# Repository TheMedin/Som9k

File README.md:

# Som9k
Principles of Digital Fabrication, group project

Soil o moisturizer 9000 is a gadget for automatically watering plants. It consists of a waterbottle, a moisture sensor, a valve controlled by a microcontroller, and a tube to guide the water.

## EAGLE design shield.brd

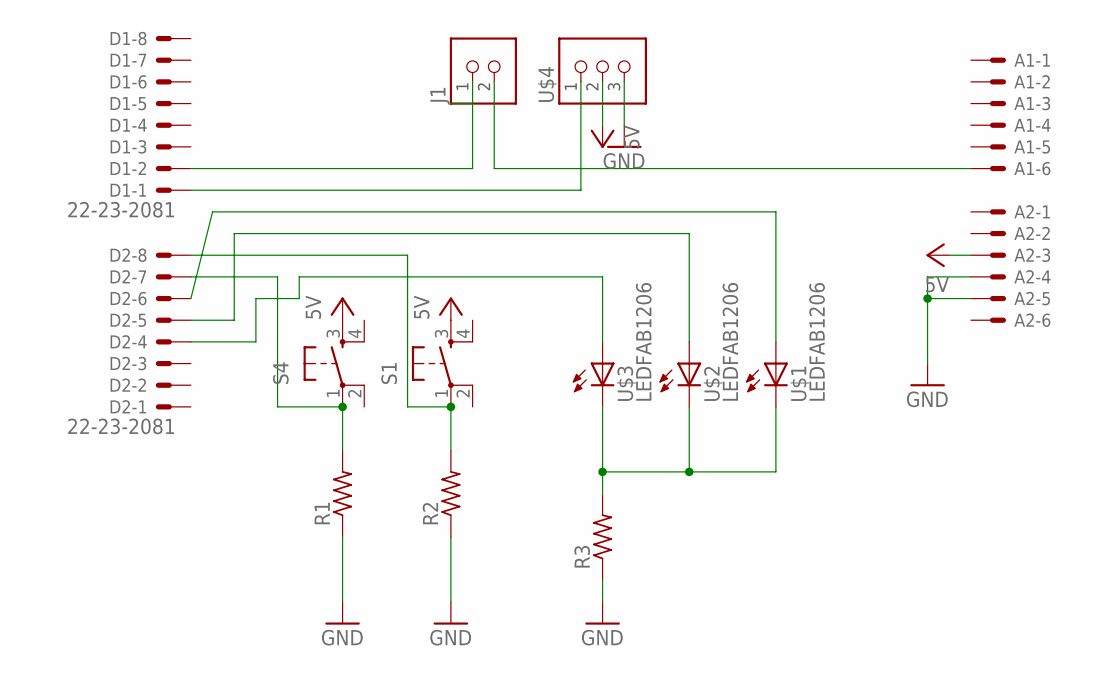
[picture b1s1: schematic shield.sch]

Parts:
A1, A2: 22-23-2061
D1, D2: 22-23-2081
J1: TERM-1X02-FABLAB; ED555DS-2DS
R1, R2, R3: RES-US1206FAB; R1206FAB
S1, S4: 6MM_SWITCH6MM_SWITCH; 6MM_SWITCH
U$1, U$2, U$3: LEDFAB1206; LED1206FAB
U$4: TERM-1X03'-FABLAB'; ED555DS-3DS

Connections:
GND: A2.4, A2.5, R1.1, R2.1, R3.1, U$4.3
unnamed: D2.8, R2.2, S1.1
unnamed: R3.2, U$1.2 (C), U$2.2 (C), U$3.2 (C)
unnamed: D2.7, R1.2, S4.1
unnamed: D1.2, J1.1
unnamed: A1.6, J1.2
unnamed: D2.6, U$1.1 (A)
unnamed: D2.5, U$2.1 (A)
unnamed: D2.4, U$3.1 (A)
unnamed: D1.1, U$4.1
VCC: A2.3, S1.3 (S), S4.3 (S), U$4.2

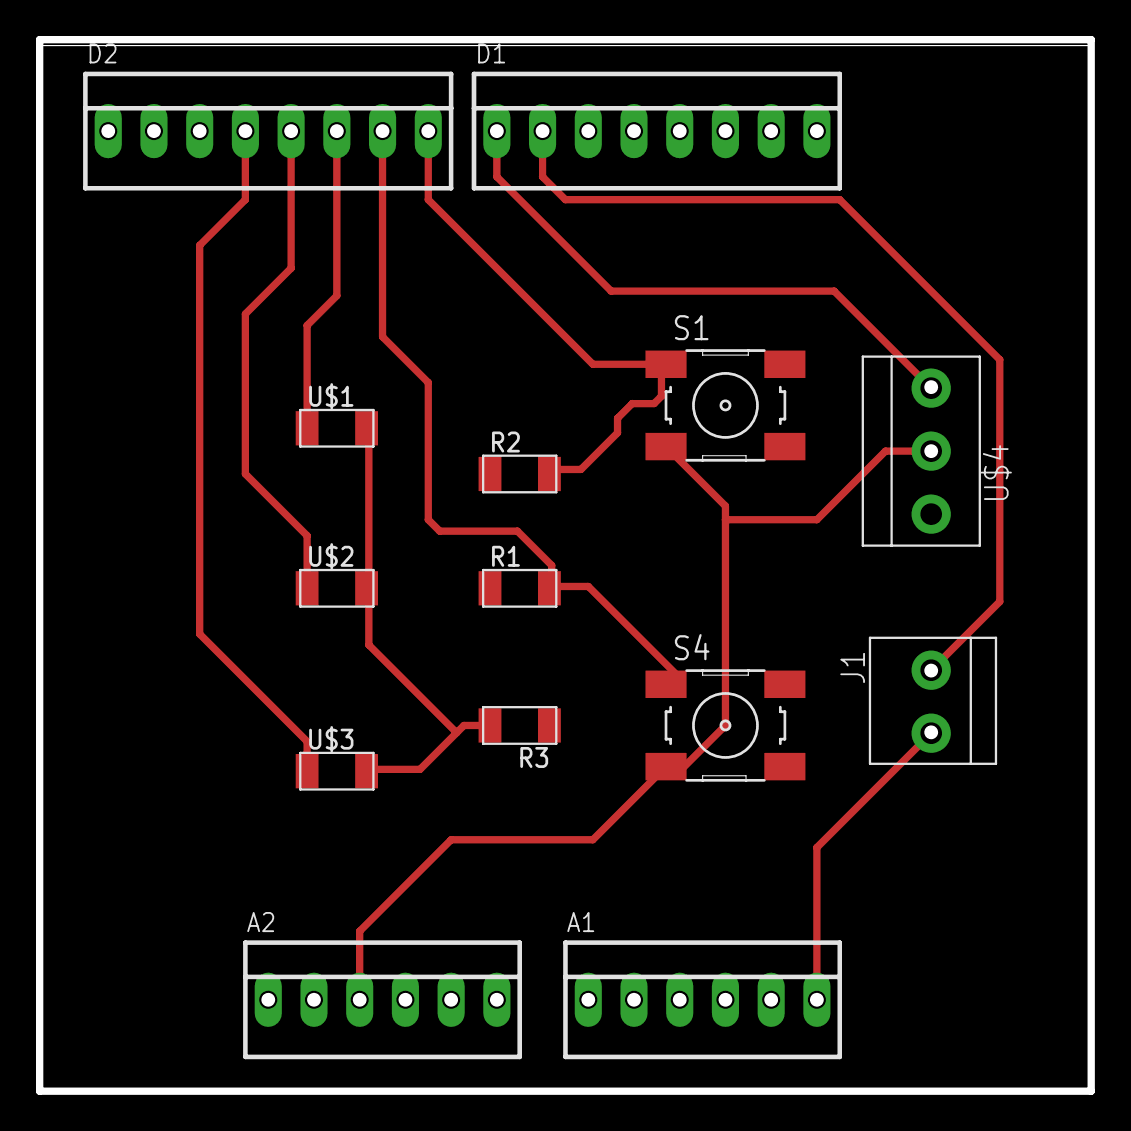
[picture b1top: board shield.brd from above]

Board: 2 copper layers, 58.4 x 58.4 mm, 14 parts (0 on the bottom side), 11 nets.

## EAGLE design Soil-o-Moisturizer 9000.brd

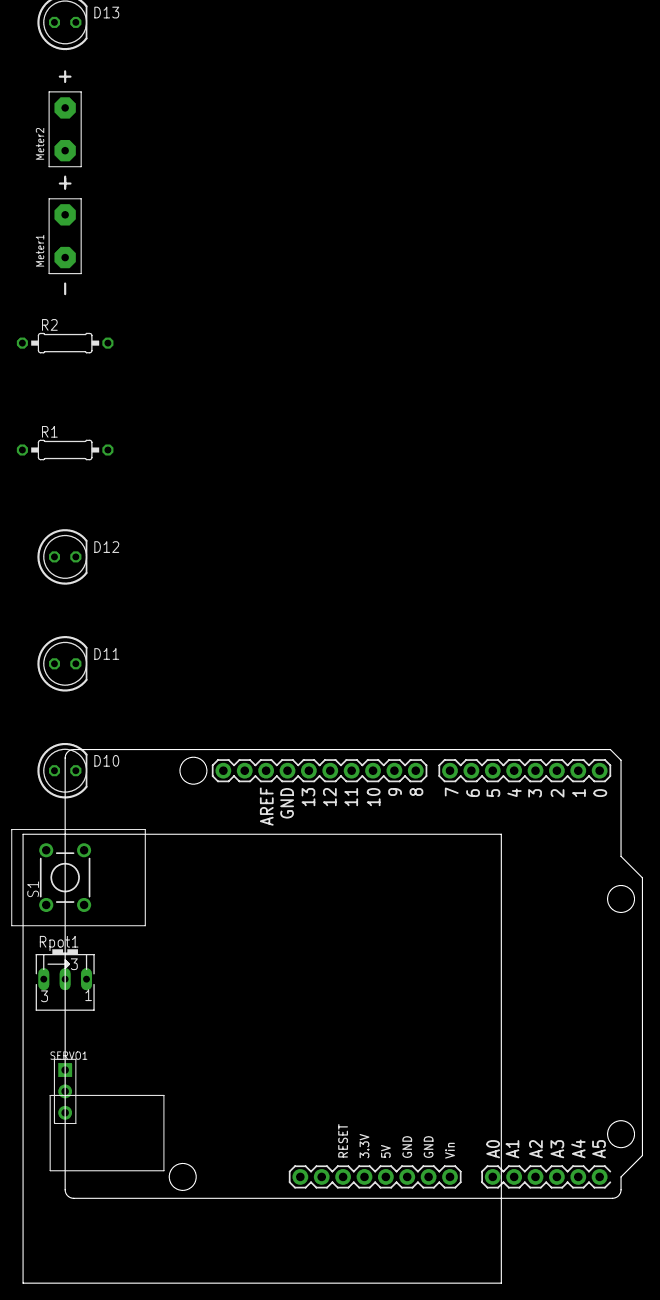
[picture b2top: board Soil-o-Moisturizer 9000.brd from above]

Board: 2 copper layers, 73.6 x 63.4 mm, 12 parts (0 on the bottom side), 12 nets, no tracks yet.

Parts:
D10, D11, D12, D13: LED5MM
Meter1, Meter2: DC-POWER
R1: 400‎Ω; 0207/10
R2: 5‎Ω; 0207/10
Rpot1: 250k‎Ω; B25V
S1: TL1105
SERVO1: 1X3P-2.54-2.54-11.6-3.0-BLACK-MALE
U1: ARDUINO_UNO

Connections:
unnamed: SERVO1.3, U1.9
unnamed: Meter1.+, Meter2.-, Rpot1.S, U1.A0
unnamed: D10.A, U1.10
unnamed: D11.A, U1.11
unnamed: D12.A, U1.12
unnamed: S1.2, U1.8
unnamed: R2.2, S1.4
unnamed: R2.1, U1.GND
unnamed: Meter2.+, Rpot1.A, S1.3, SERVO1.2, U1.5V
unnamed: D13.A, U1.13
unnamed: D10.K, D11.K, D12.K, D13.K, R1.2
unnamed: Meter1.-, R1.1, Rpot1.E, SERVO1.1, U1.GND..

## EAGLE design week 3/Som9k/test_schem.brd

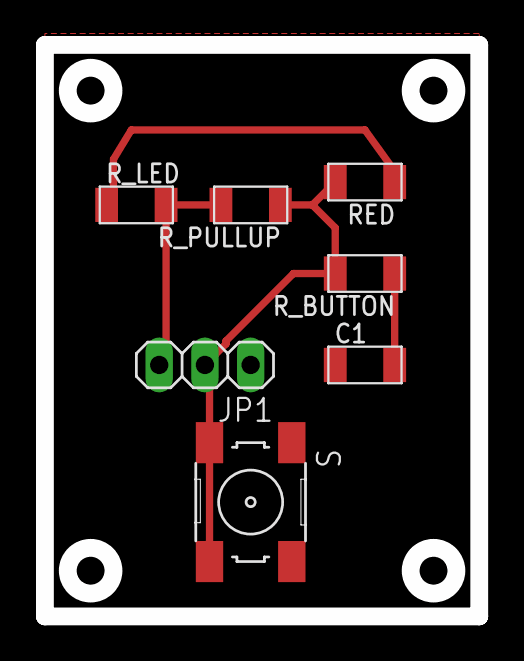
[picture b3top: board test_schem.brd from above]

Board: 2 copper layers, 24.1 x 32.1 mm, 7 parts (0 on the bottom side), 5 nets.

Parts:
C1: 10nF; C1206FAB
JP1: 1X03
RED: LED1206FAB
R_BUTTON: 49.9k; R1206FAB
R_LED: 499; R1206FAB
R_PULLUP: 49.9k; R1206FAB
S: 6MM_SWITCH

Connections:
+5V: JP1.3, R_LED.2, R_PULLUP.2
BUTTON: JP1.2, RED.2, R_BUTTON.2, R_PULLUP.1, S.3, S.4
GND: C1.1, JP1.1, S.1, S.2
unnamed: RED.1, R_LED.1
unnamed: C1.2, R_BUTTON.1

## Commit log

2018-03-23 Added short description
2018-03-23 added picture
2018-04-11 eagle files plus images
2018-04-11 reordering happened
2018-04-15 UI sketches
2018-04-15 parts1.jpg
2018-04-17 mid-term presentation
2018-04-30 Arduino-UNO code
2018-04-30 päivitetty arduino koodi
2018-04-30 eagle-brd from tinkercad
2018-05-02 calibrate implemented
2018-05-04 Add files via upload
    first complete sketch of the open/close mechanism
2018-05-08 shieldi
2018-05-08 Add files via upload
    fablab millaukset
2018-05-09 final presentation
2018-05-29 som9k.ino demossa käytetty koodi
2018-05-31 lopullinen käyttöliittymäkoodi
